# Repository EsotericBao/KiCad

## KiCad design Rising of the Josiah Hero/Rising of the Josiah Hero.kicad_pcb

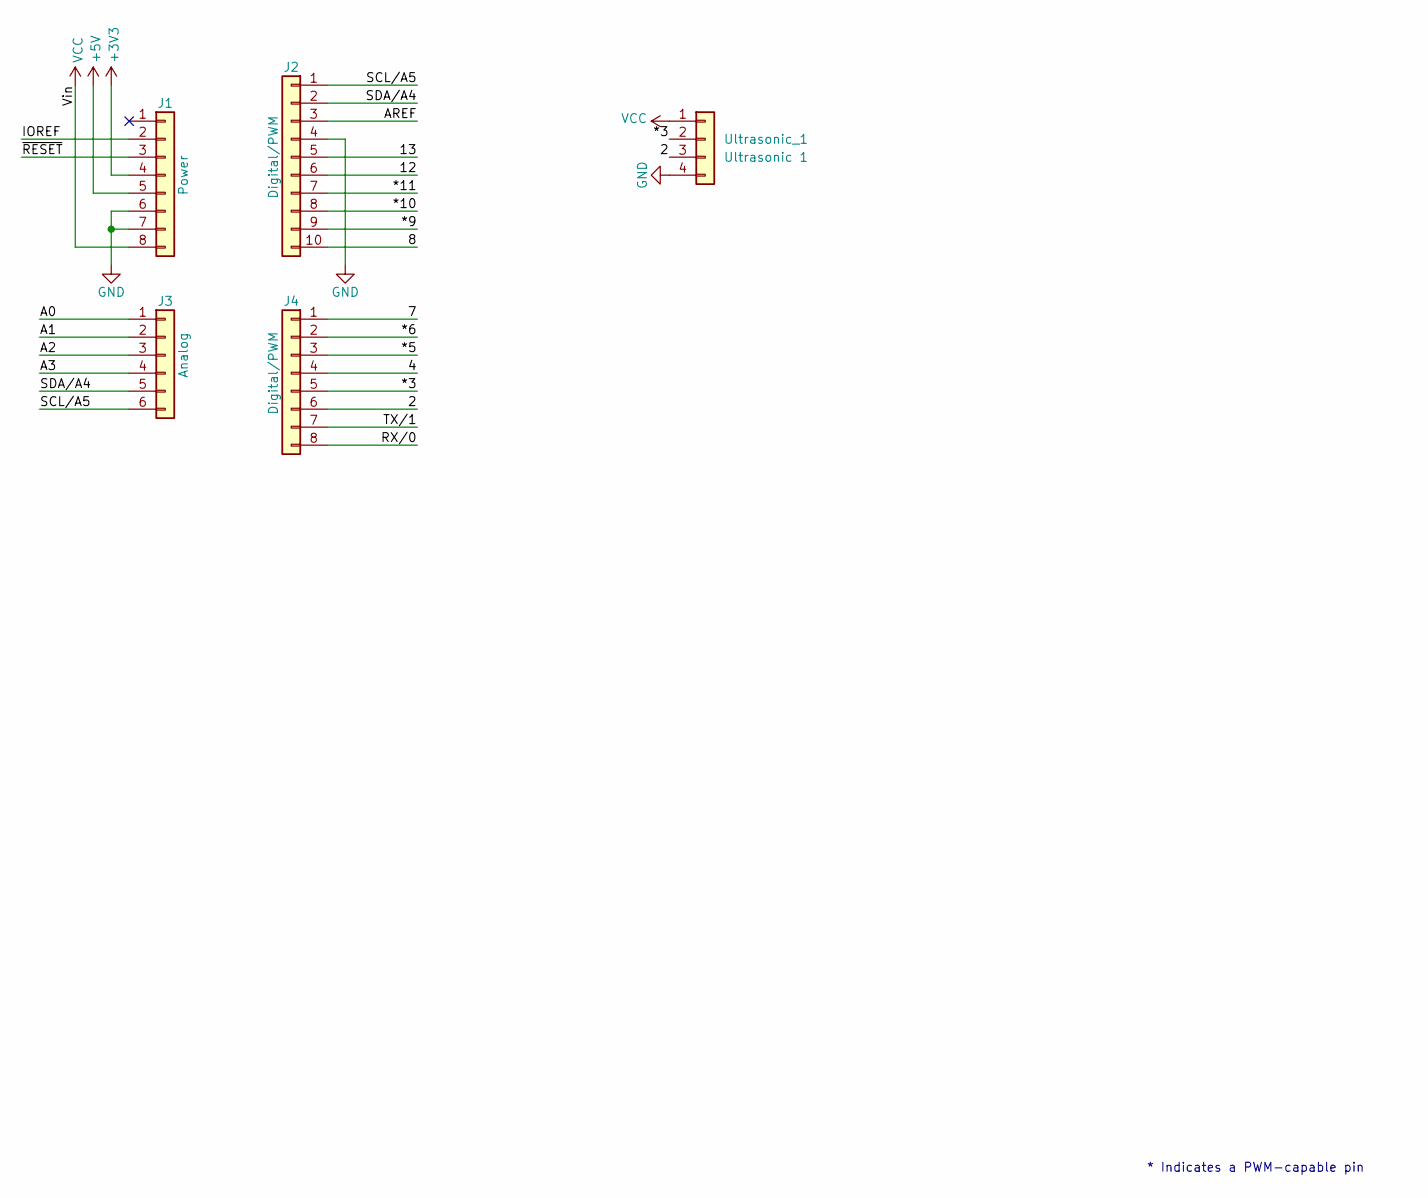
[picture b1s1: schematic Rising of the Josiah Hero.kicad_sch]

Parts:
J1: Power; PinSocket_1x08_P2.54mm_Vertical
J2: Digital/PWM; PinSocket_1x10_P2.54mm_Vertical
J3: Analog; PinSocket_1x06_P2.54mm_Vertical
J4: Digital/PWM; PinSocket_1x08_P2.54mm_Vertical
Ultrasonic_1: Ultrasonic 1; JST_XH_B4B-XH-A_1x04_P2.50mm_Vertical

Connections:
+3V3: J1.4
+5V: J1.5
/2: J4.6, Ultrasonic_1.3
/4: J4.4
/7: J4.1
/8: J2.10
/12: J2.6
/13: J2.5
/*3: J4.5, Ultrasonic_1.2
/*5: J4.3
/*6: J4.2
/*9: J2.9
/*10: J2.8
/*11: J2.7
/A0: J3.1
/A1: J3.2
/A2: J3.3
/A3: J3.4
/AREF: J2.3
/IOREF: J1.2
/RX/0: J4.8
/SCL/A5: J2.1, J3.6
/SDA/A4: J2.2, J3.5
/TX/1: J4.7
/~RESET: J1.3
GND: J1.6, J1.7, J2.4, Ultrasonic_1.4
VCC: J1.8, Ultrasonic_1.1

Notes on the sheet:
* Indicates a PWM-capable pin

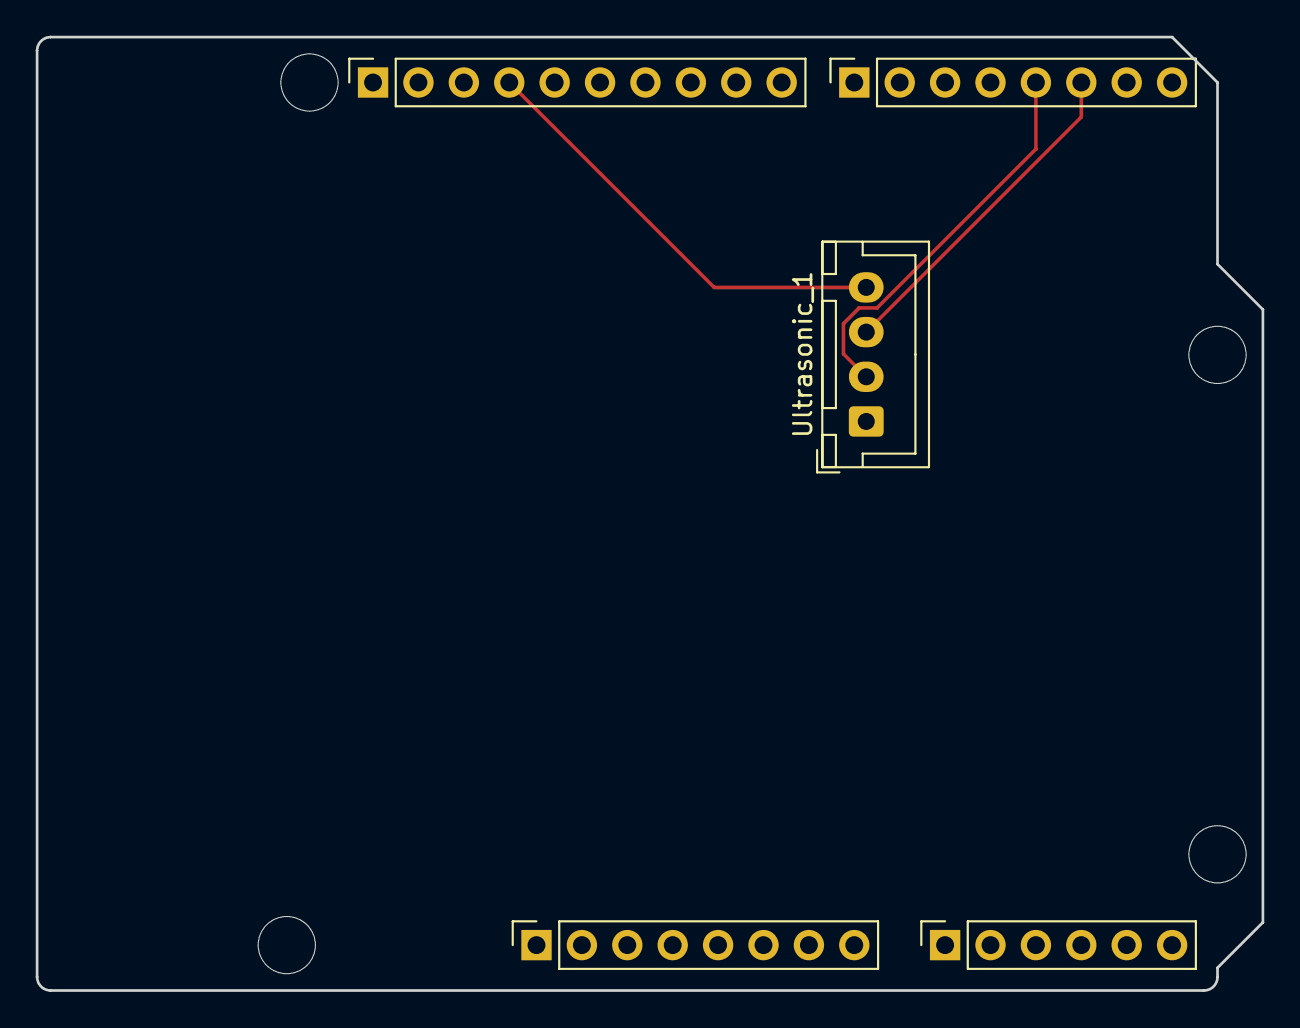
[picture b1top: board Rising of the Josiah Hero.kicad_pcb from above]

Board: 2 copper layers, 68.6 x 53.3 mm, 9 parts (0 on the bottom side), 6 nets.

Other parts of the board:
MH1, MH2, MH3, MH4: MountingHole_3.2mm

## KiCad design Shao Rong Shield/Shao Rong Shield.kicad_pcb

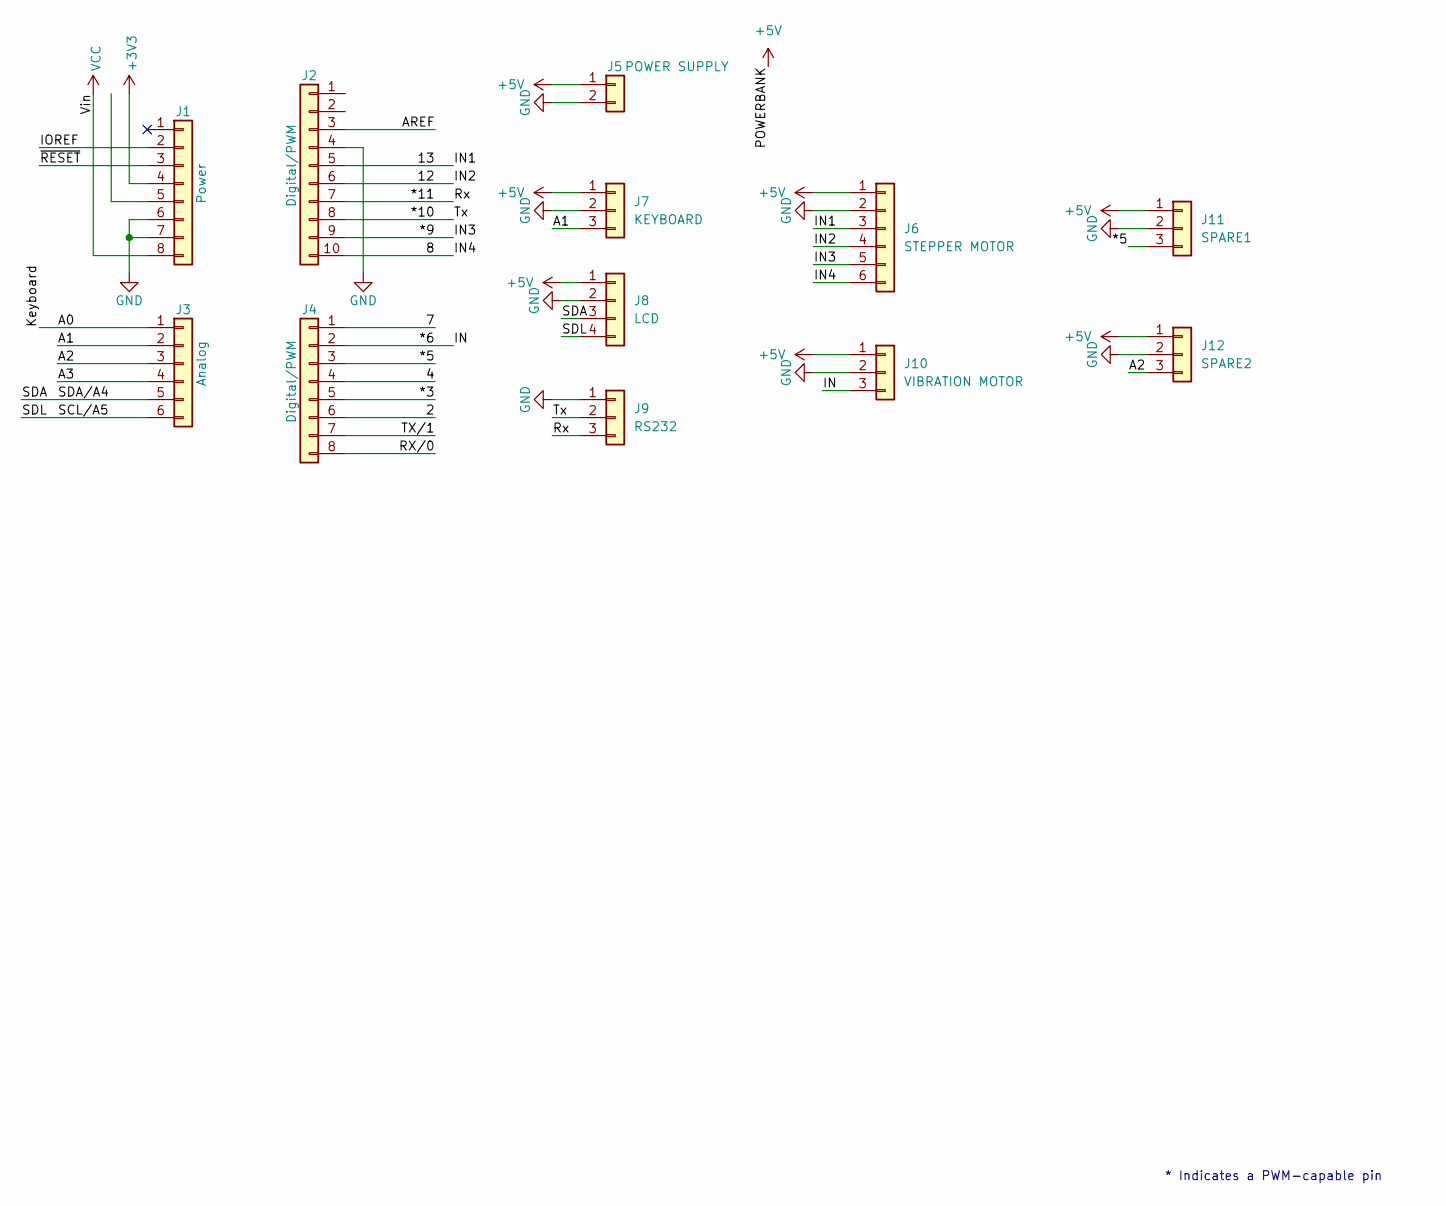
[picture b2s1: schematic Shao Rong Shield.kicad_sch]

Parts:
J1: Power; PinSocket_1x08_P2.54mm_Vertical
J2: Digital/PWM; PinSocket_1x10_P2.54mm_Vertical
J3: Analog; PinSocket_1x06_P2.54mm_Vertical
J4: Digital/PWM; PinSocket_1x08_P2.54mm_Vertical
J5: POWER SUPPLY; JST_XH_S2B-XH-A_1x02_P2.50mm_Horizontal
J6: STEPPER MOTOR; JST_XH_B6B-XH-A_1x06_P2.50mm_Vertical
J7: KEYBOARD; JST_XH_B3B-XH-A_1x03_P2.50mm_Vertical
J8: LCD; JST_XH_B4B-XH-A_1x04_P2.50mm_Vertical
J9: RS232; JST_XH_B3B-XH-A_1x03_P2.50mm_Vertical
J10: VIBRATION MOTOR; JST_XH_B3B-XH-A_1x03_P2.50mm_Vertical
J11: SPARE1; JST_XH_B3B-XH-A_1x03_P2.50mm_Vertical
J12: SPARE2; JST_XH_B3B-XH-A_1x03_P2.50mm_Vertical

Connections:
+3V3: J1.4
+5V: J5.1, J6.1, J7.1, J8.1, J10.1, J11.1, J12.1
/2: J4.6
/4: J4.4
/7: J4.1
/8: J2.10, J6.6
/12: J2.6, J6.4
/13: J2.5, J6.3
/*3: J4.5
/*5: J4.3, J11.3
/*6: J4.2, J10.3
/*9: J2.9, J6.5
/*10: J2.8, J9.2
/*11: J2.7, J9.3
/A0: J3.1
/A1: J3.2, J7.3
/A2: J3.3, J12.3
/A3: J3.4
/AREF: J2.3
/IOREF: J1.2
/RX/0: J4.8
/SCL/A5: J3.6, J8.4
/SDA: J3.5, J8.3
/TX/1: J4.7
/~RESET: J1.3
GND: J1.6, J1.7, J2.4, J5.2, J6.2, J7.2, J8.2, J9.1, J10.2, J11.2, J12.2
VCC: J1.8

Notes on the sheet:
* Indicates a PWM-capable pin

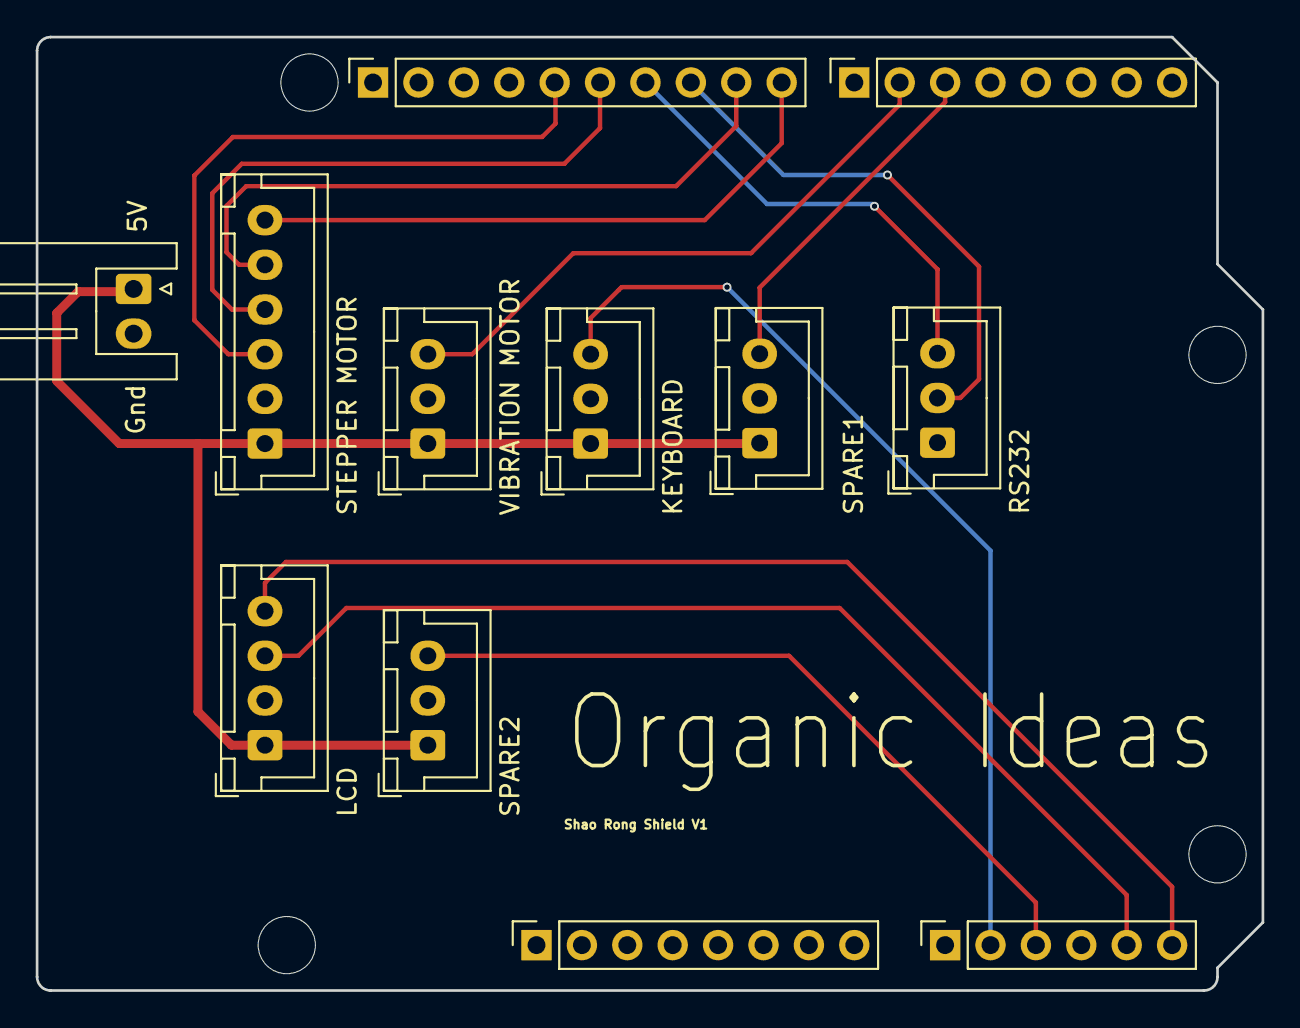
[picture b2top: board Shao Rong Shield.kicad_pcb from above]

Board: 2 copper layers, 68.6 x 53.3 mm, 16 parts (0 on the bottom side), 14 nets.

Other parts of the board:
MH1, MH2, MH3, MH4: MountingHole_3.2mm

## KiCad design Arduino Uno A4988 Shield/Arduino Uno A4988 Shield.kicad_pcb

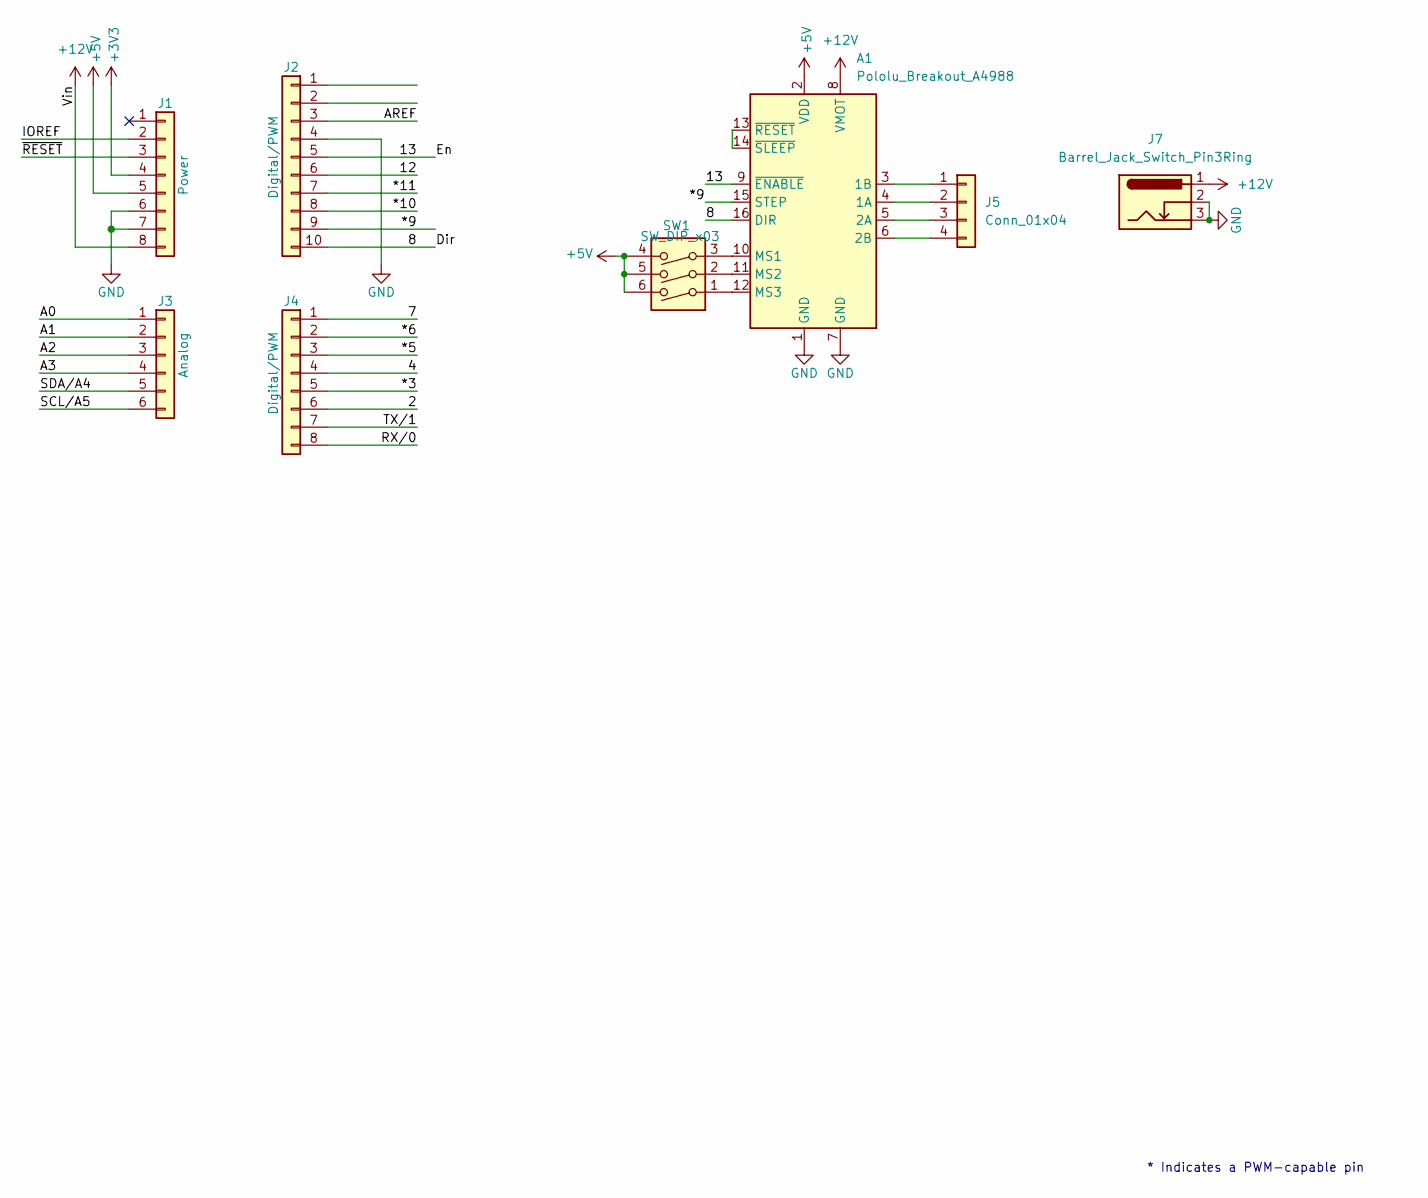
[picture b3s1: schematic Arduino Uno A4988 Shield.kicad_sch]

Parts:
A1: Pololu_Breakout_A4988; Pololu_Breakout-16_15.2x20.3mm
J1: Power; PinSocket_1x08_P2.54mm_Vertical
J2: Digital/PWM; PinSocket_1x10_P2.54mm_Vertical
J3: Analog; PinSocket_1x06_P2.54mm_Vertical
J4: Digital/PWM; PinSocket_1x08_P2.54mm_Vertical
J5: Conn_01x04; PinHeader_1x04_P2.54mm_Vertical
J7: Barrel_Jack_Switch_Pin3Ring; BarrelJack_GCT_DCJ200-10-A_Horizontal
SW1: SW_DIP_x03; SW_DIP_SPSTx03_Slide_6.7x9.18mm_W8.61mm_P2.54mm_LowProfile

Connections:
+3V3: J1.4
+5V: A1.2 (VDD), J1.5, SW1.4, SW1.5, SW1.6
+12V: A1.8 (VMOT), J1.8, J7.1
/2: J4.6
/4: J4.4
/7: J4.1
/8: A1.16 (DIR), J2.10
/12: J2.6
/13: A1.9 (~ENABLE), J2.5
/*3: J4.5
/*5: J4.3
/*6: J4.2
/*9: A1.15 (STEP), J2.9
/*10: J2.8
/*11: J2.7
/A0: J3.1
/A1: J3.2
/A2: J3.3
/A3: J3.4
/AREF: J2.3
/IOREF: J1.2
/RX/0: J4.8
/SCL/A5: J3.6
/SDA/A4: J3.5
/TX/1: J4.7
/~RESET: J1.3
GND: A1.1 (GND), A1.7 (GND), J1.6, J1.7, J2.4, J7.2, J7.3
unnamed: A1.4 (1A), J5.2
unnamed: A1.3 (1B), J5.1
unnamed: A1.5 (2A), J5.3
unnamed: A1.6 (2B), J5.4
unnamed: A1.10 (MS1), SW1.3
unnamed: A1.11 (MS2), SW1.2
unnamed: A1.12 (MS3), SW1.1
unnamed: A1.13 (~RESET), A1.14 (~SLEEP)

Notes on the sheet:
* Indicates a PWM-capable pin

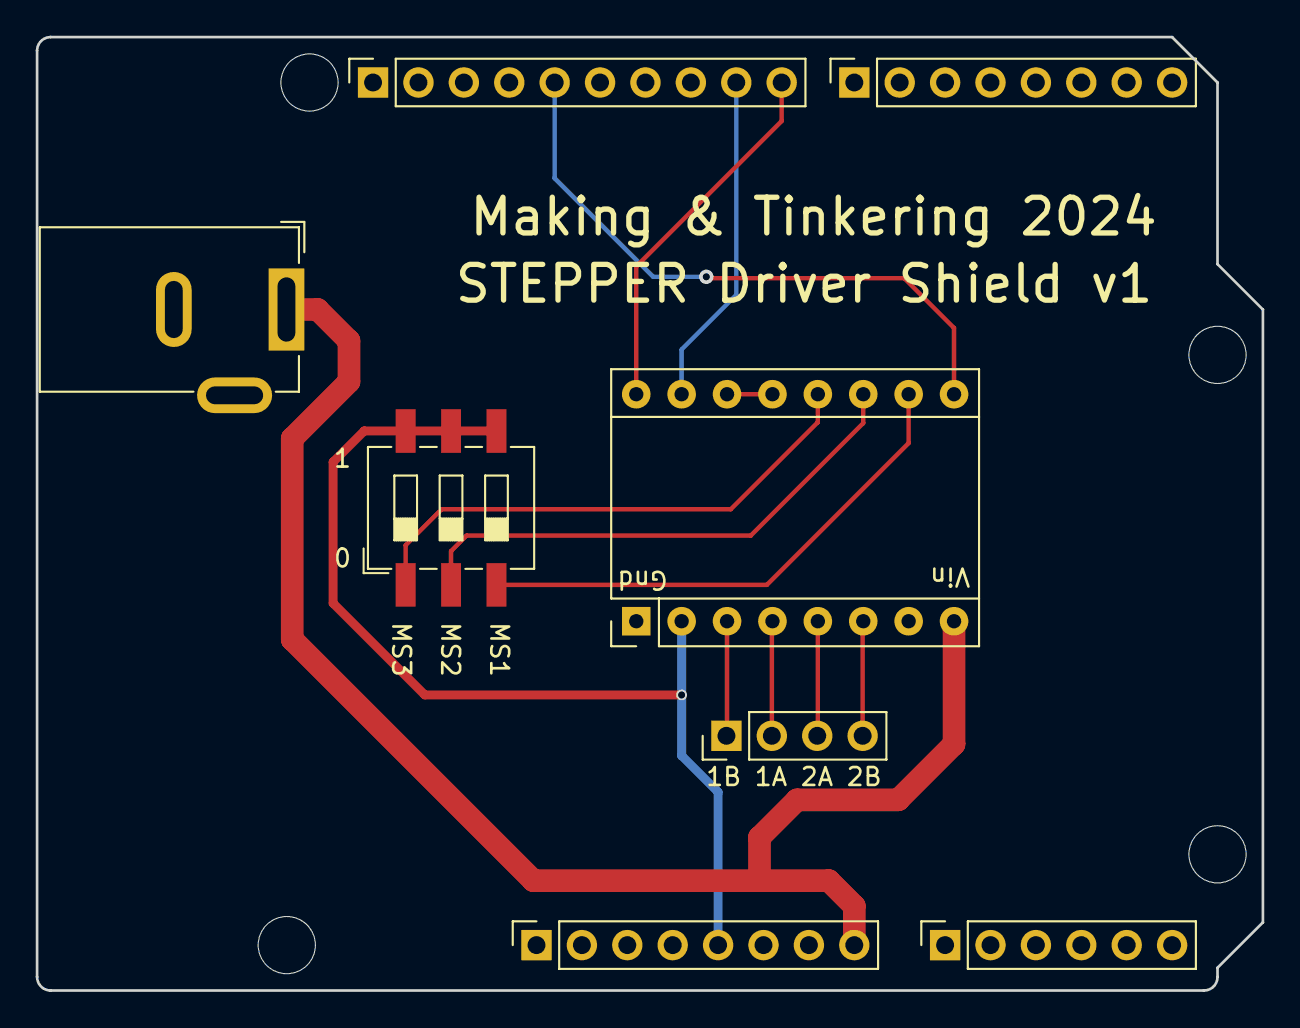
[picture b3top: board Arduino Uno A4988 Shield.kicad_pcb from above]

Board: 2 copper layers, 68.6 x 53.3 mm, 12 parts (0 on the bottom side), 14 nets.

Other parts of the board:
MH1, MH2, MH3, MH4: MountingHole_3.2mm

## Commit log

2024-07-20 created first project
2024-07-20 created driver shield project
2024-07-21 added template
2024-07-22 Created template
2024-07-22 First prototype
2024-07-22 organised pcb
2024-07-23 Completed Shaorong and A4988 Shield
2024-07-29 Josiah burden
